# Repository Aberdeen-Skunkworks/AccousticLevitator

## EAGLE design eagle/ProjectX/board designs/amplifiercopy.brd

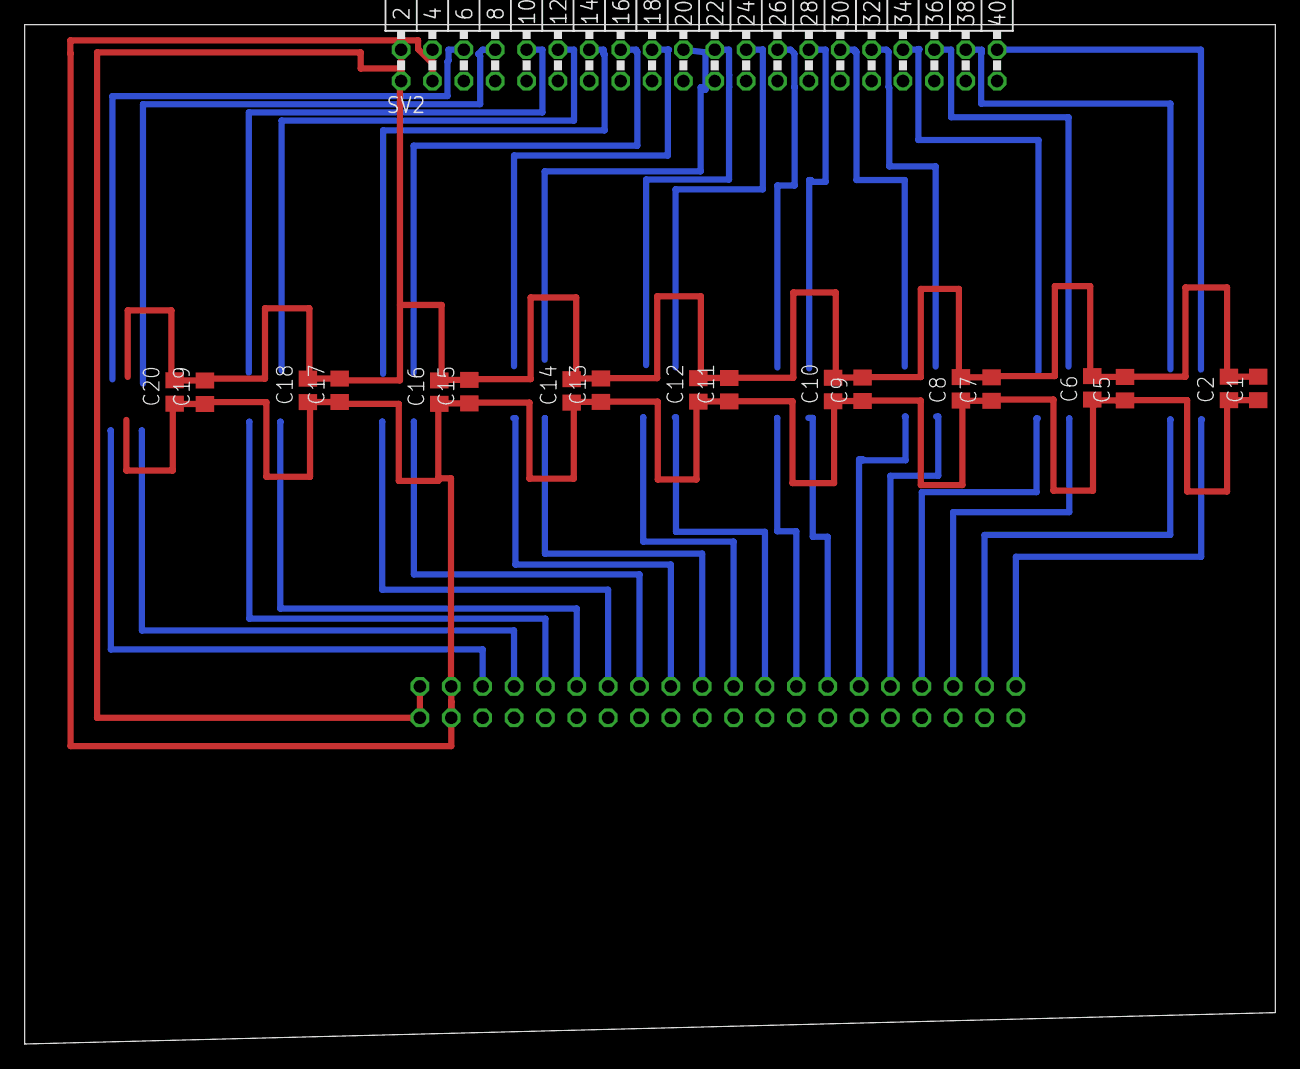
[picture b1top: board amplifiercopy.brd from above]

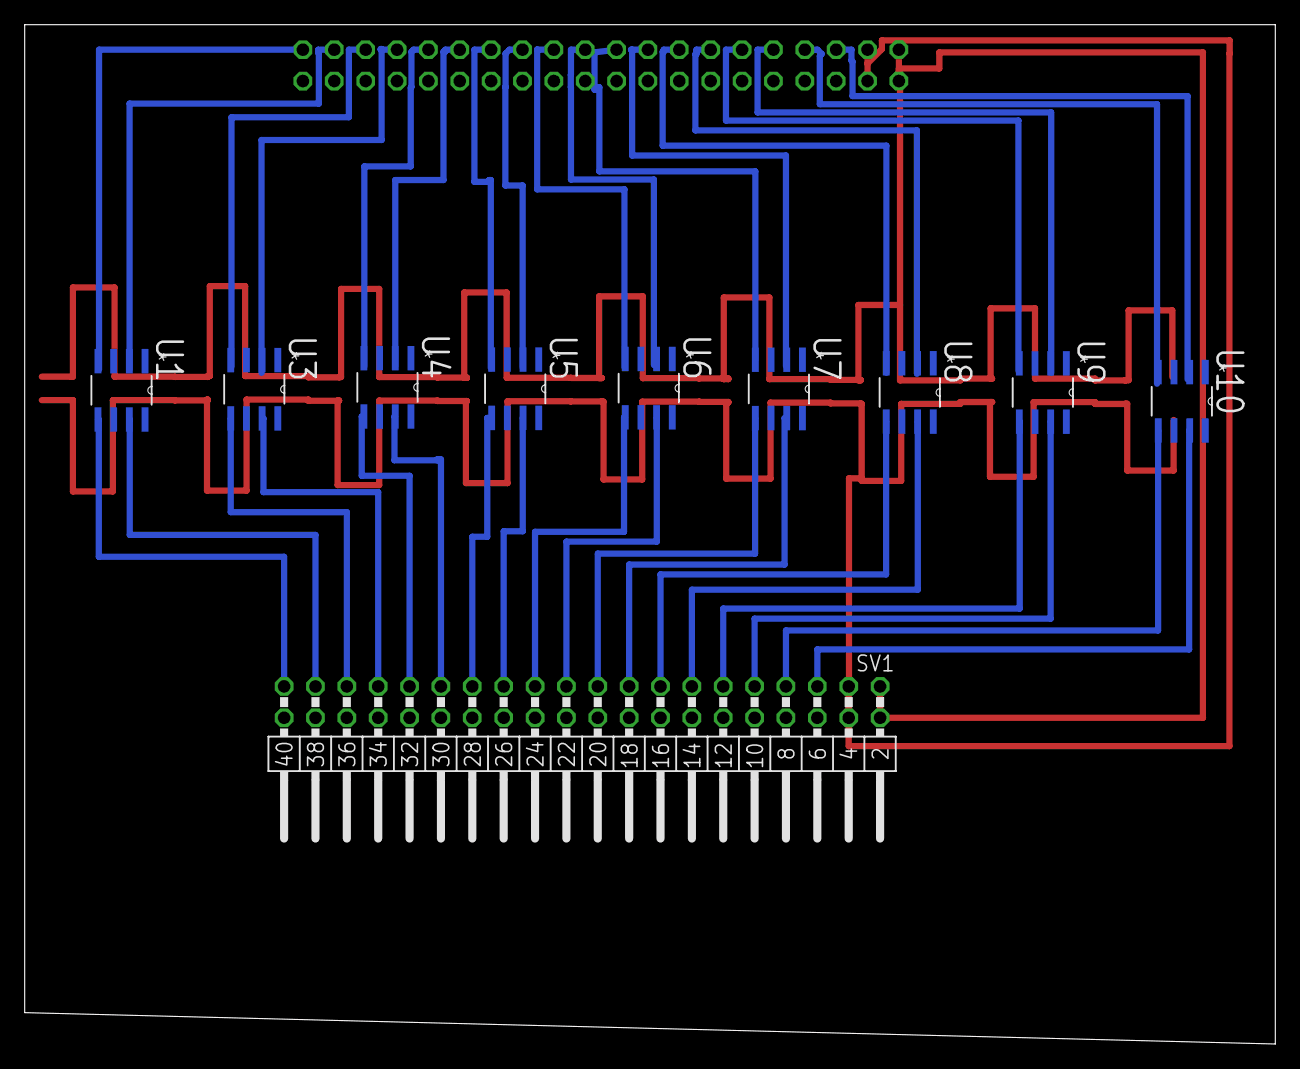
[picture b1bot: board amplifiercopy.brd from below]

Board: 2 copper layers, 101.3 x 82.5 mm, 29 parts (10 on the bottom side), 38 nets.

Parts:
C1, C5, C7, C9, C11, C13, C15, C17, C19: 4.7uF; C0805
C2, C6, C8, C10, C12, C14, C16, C18, C20: 100nF; C0805
SV1, SV2: MA20-2W
U1, U3, U4, U5, U6, U7, U8, U9, U10: TC4427COA; SOIC127P600X175-8N

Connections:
GND: C1.2, C2.2, C5.2, C6.2, C7.2, C8.2, C9.2, C10.2, C11.2, C12.2, C13.2, C14.2, C15.2, C16.2, C17.2, C18.2, C19.2, C20.2, SV1.1, SV1.2, SV2.1, SV2.2, U1.3, U3.3, U4.3, U5.3, U6.3, U7.3, U8.3, U9.3, U10.3
unnamed: SV2.36, U3.4
unnamed: SV1.39, U1.5
unnamed: SV1.37, U1.7
unnamed: SV2.40, U1.4
unnamed: SV2.38, U1.2
unnamed: SV2.34, U3.2
unnamed: SV1.35, U3.5
unnamed: SV1.33, U3.7
unnamed: SV2.32, U4.4
unnamed: SV2.30, U4.2
unnamed: SV1.31, U4.5
unnamed: SV1.29, U4.7
unnamed: SV1.27, U5.5
unnamed: SV1.25, U5.7
unnamed: SV2.28, U5.4
unnamed: SV2.26, U5.2
unnamed: SV1.23, U6.5
unnamed: SV1.21, U6.7
unnamed: SV2.24, U6.4
unnamed: SV2.22, U6.2
unnamed: SV1.19, U7.5
unnamed: SV1.17, U7.7
unnamed: SV2.20, U7.4
unnamed: SV1.15, U8.5
unnamed: SV1.13, U8.7
unnamed: SV2.18, U7.2
unnamed: SV2.16, U8.4
unnamed: SV2.14, U8.2
unnamed: SV2.12, U9.4
unnamed: SV1.11, U9.5
unnamed: SV1.9, U9.7
unnamed: SV2.10, U9.2
unnamed: SV2.8, U10.4
unnamed: SV1.5, U10.7
unnamed: SV1.7, U10.5
unnamed: SV2.6, U10.2
VCC: C1.1, C2.1, C5.1, C6.1, C7.1, C8.1, C9.1, C10.1, C11.1, C12.1, C13.1, C14.1, C15.1, C16.1, C17.1, C18.1, C19.1, C20.1, SV1.3, SV1.4, SV2.3, SV2.4, U1.6, U3.6, U4.6, U5.6, U6.6, U7.6, U8.6, U9.6, U10.6

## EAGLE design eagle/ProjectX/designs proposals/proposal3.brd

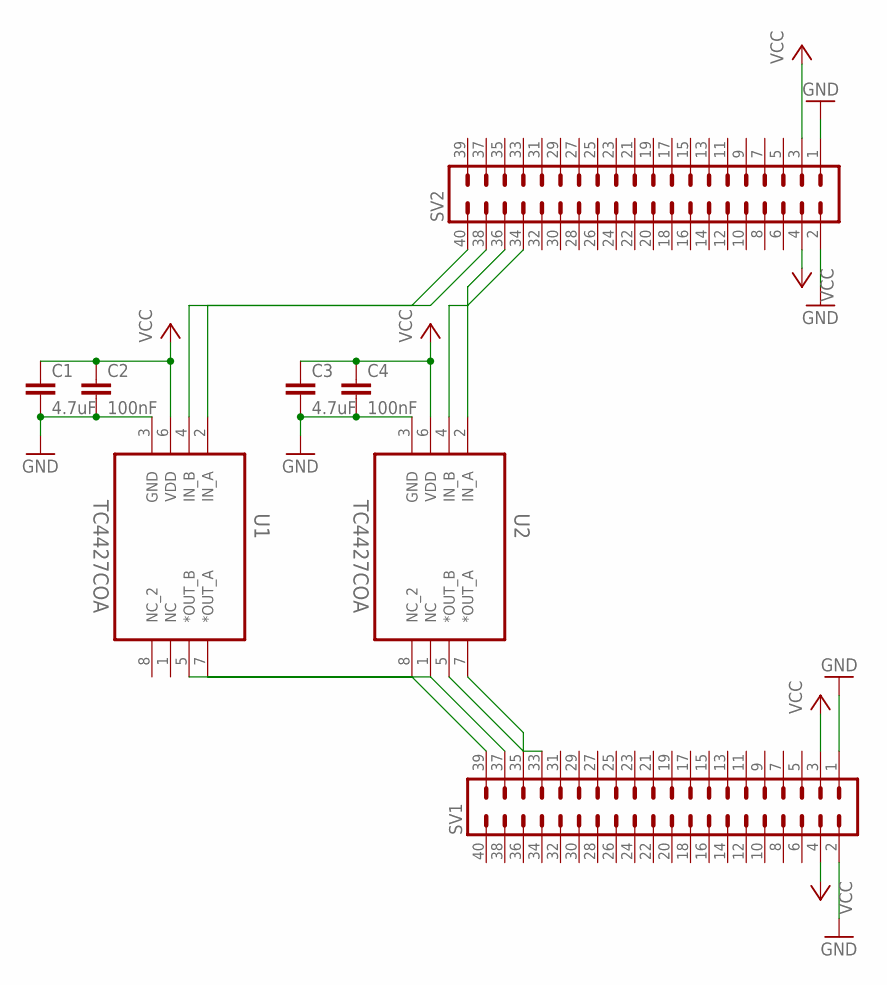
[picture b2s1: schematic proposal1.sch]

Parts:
C1, C3: 4.7uF; C0805
C2, C4: 100nF; C0805
SV1, SV2: MA20-2W
U1, U2: TC4427COA; SOIC127P600X175-8N

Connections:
GND: C1.2, C2.2, C3.2, C4.2, SV1.1, SV1.2, SV2.1, SV2.2, U1.3 (GND), U2.3 (GND)
unnamed: SV2.34, U2.4 (IN_B)
unnamed: SV1.39, U1.7 (*OUT_A)
unnamed: SV1.37, U1.5 (*OUT_B)
unnamed: SV2.38, U1.4 (IN_B)
unnamed: SV2.40, U1.2 (IN_A)
unnamed: SV2.36, U2.2 (IN_A)
unnamed: SV1.35, U2.7 (*OUT_A)
unnamed: SV1.33, U2.5 (*OUT_B)
VCC: C1.1, C2.1, C3.1, C4.1, SV1.3, SV1.4, SV2.3, SV2.4, U1.6 (VDD), U2.6 (VDD)

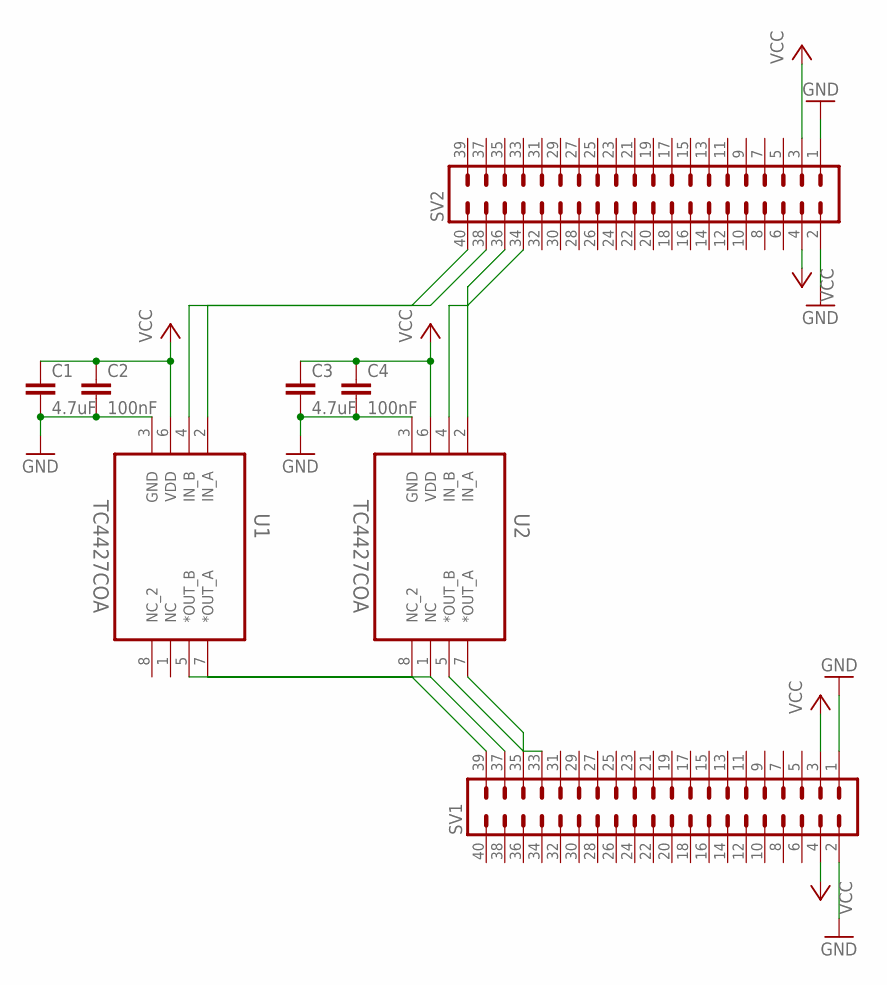
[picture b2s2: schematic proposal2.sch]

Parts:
C1, C3: 4.7uF; C0805
C2, C4: 100nF; C0805
SV1, SV2: MA20-2W
U1, U2: TC4427COA; SOIC127P600X175-8N

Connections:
GND: C1.2, C2.2, C3.2, C4.2, SV1.1, SV1.2, SV2.1, SV2.2, U1.3 (GND), U2.3 (GND)
unnamed: SV2.34, U2.4 (IN_B)
unnamed: SV1.39, U1.7 (*OUT_A)
unnamed: SV1.37, U1.5 (*OUT_B)
unnamed: SV2.38, U1.4 (IN_B)
unnamed: SV2.40, U1.2 (IN_A)
unnamed: SV2.36, U2.2 (IN_A)
unnamed: SV1.35, U2.7 (*OUT_A)
unnamed: SV1.33, U2.5 (*OUT_B)
VCC: C1.1, C2.1, C3.1, C4.1, SV1.3, SV1.4, SV2.3, SV2.4, U1.6 (VDD), U2.6 (VDD)

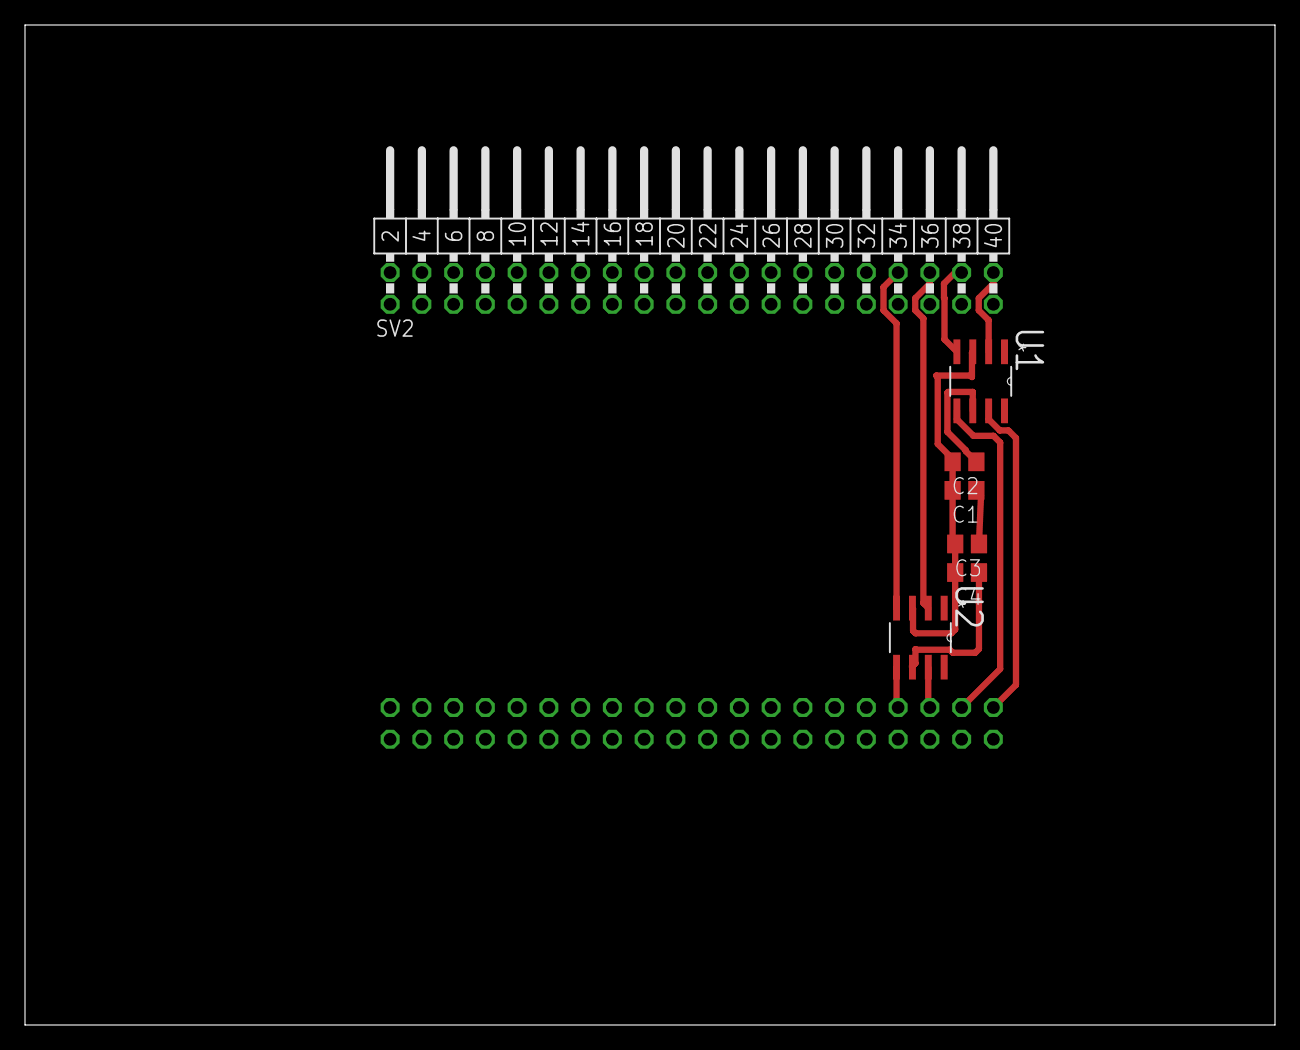
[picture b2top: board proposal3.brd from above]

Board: 2 copper layers, 100.0 x 80.0 mm, 8 parts (1 on the bottom side), 10 nets.

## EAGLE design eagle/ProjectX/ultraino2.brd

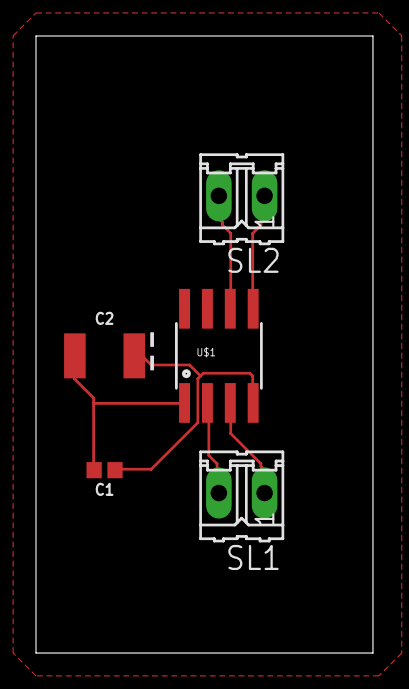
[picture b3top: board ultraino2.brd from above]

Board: 2 copper layers, 18.7 x 34.3 mm, 5 parts (0 on the bottom side), 6 nets.

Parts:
C1: 0.1uF; 0402
C2: 47uF; EIA3528
SL1, SL2: 02P
U$1: TC4427; SOIC-8

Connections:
unnamed: SL1.2, U$1.2
unnamed: SL1.1, U$1.3
unnamed: SL2.1, U$1.5
unnamed: SL2.2, U$1.6
PE: C1.1, C2.A, U$1.4
VCC: C1.2, C2.C, U$1.1

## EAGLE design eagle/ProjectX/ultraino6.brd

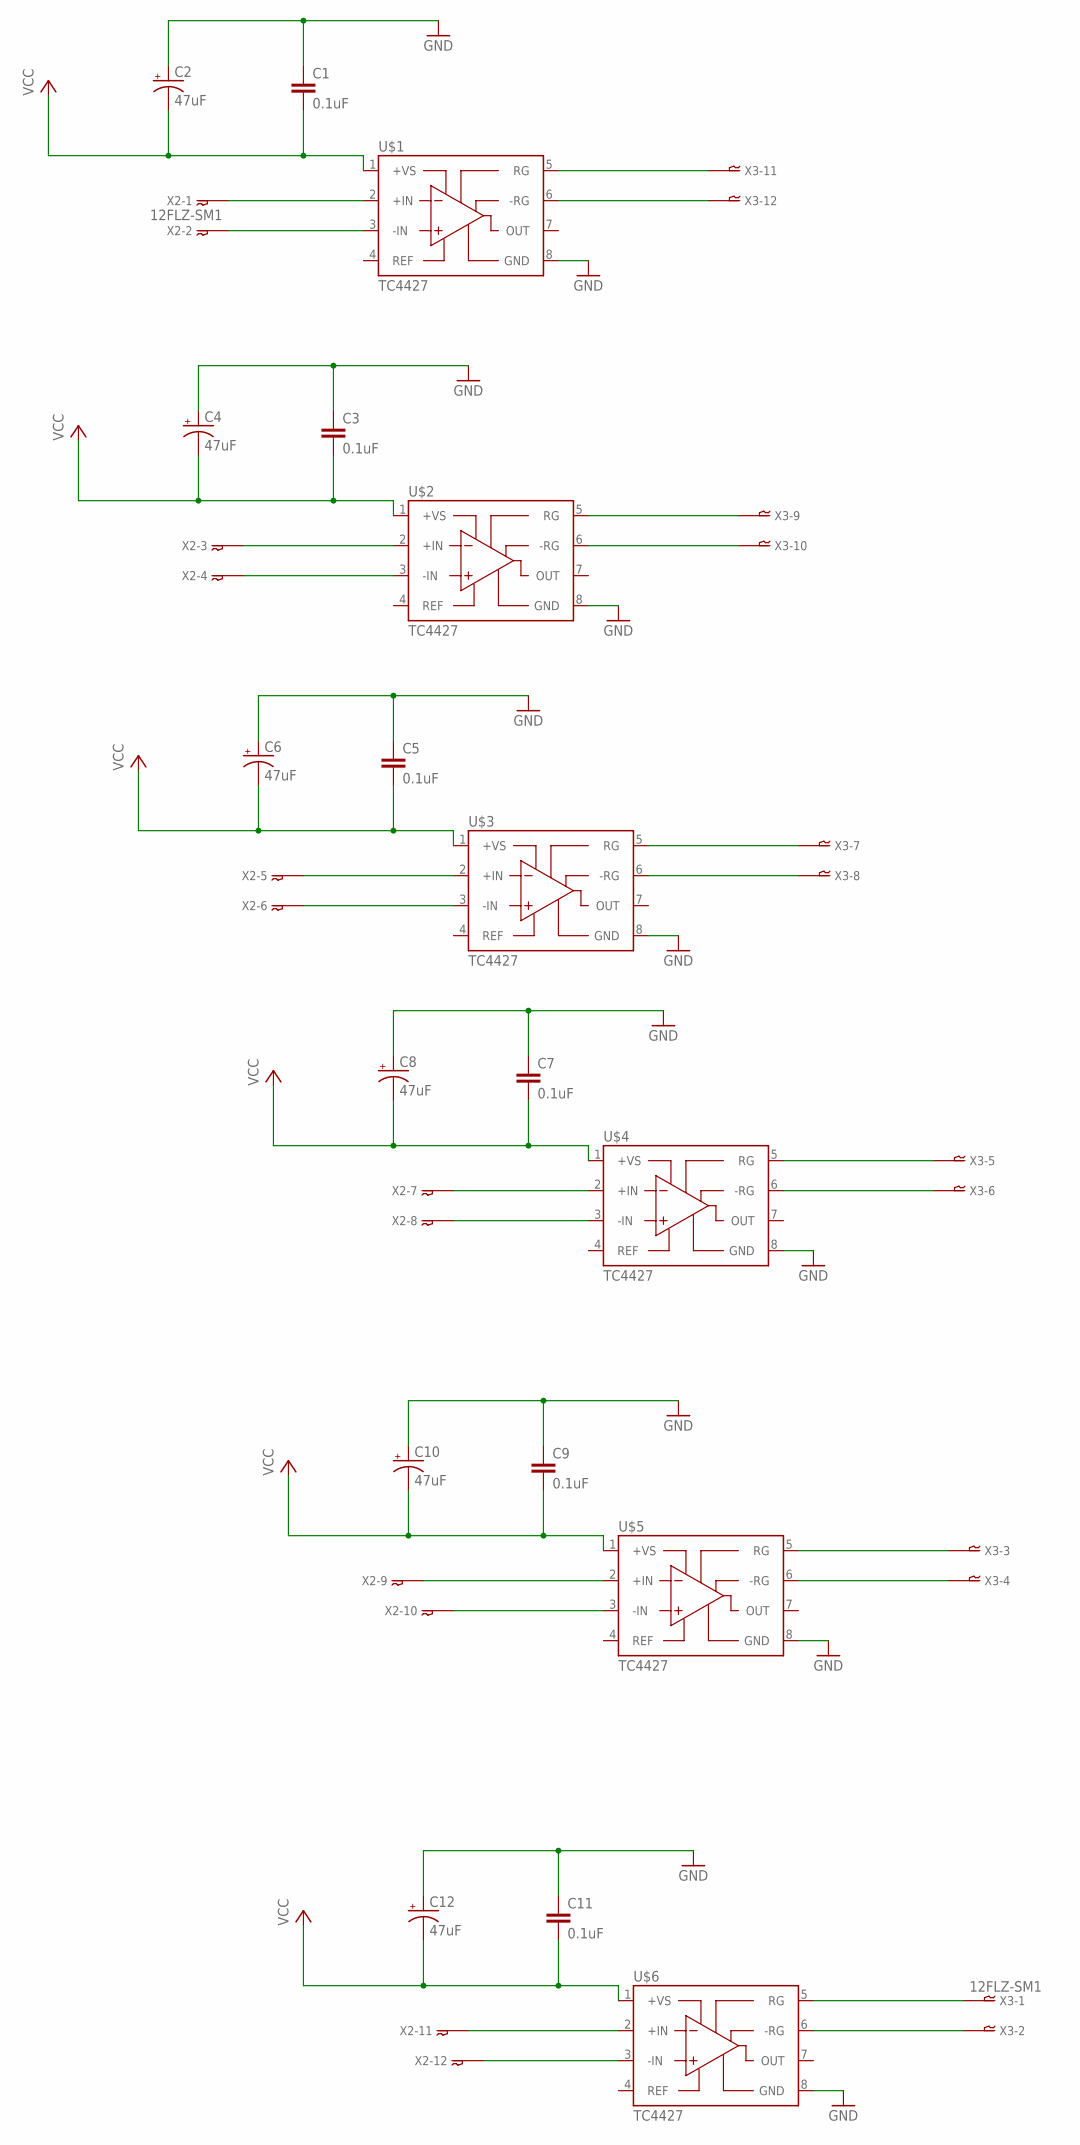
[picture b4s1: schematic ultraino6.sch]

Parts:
C1, C3, C5, C7, C9, C11: 0.1uF; 0402
C2, C4, C6, C8, C10, C12: 47uF; EIA3528
U$1, U$2, U$3, U$4, U$5, U$6: TC4427; SOIC-8
X2, X3: 12FLZ-SM1; 12FLZ-SM

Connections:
GND: C1.1, C2.A (+), C3.1, C4.A (+), C5.1, C6.A (+), C7.1, C8.A (+), C9.1, C10.A (+), C11.1, C12.A (+), U$1.8 (GND), U$2.8 (GND), U$3.8 (GND), U$4.8 (GND), U$5.8 (GND), U$6.8 (GND)
unnamed: U$1.2 (+IN), X2.1
unnamed: U$1.3 (-IN), X2.2
unnamed: U$1.5 (RG), X3.11
unnamed: U$1.6 (-RG), X3.12
unnamed: U$2.2 (+IN), X2.3
unnamed: U$2.5 (RG), X3.9
unnamed: U$2.6 (-RG), X3.10
unnamed: U$2.3 (-IN), X2.4
unnamed: U$3.2 (+IN), X2.5
unnamed: U$3.5 (RG), X3.7
unnamed: U$3.6 (-RG), X3.8
unnamed: U$3.3 (-IN), X2.6
unnamed: U$4.2 (+IN), X2.7
unnamed: U$4.5 (RG), X3.5
unnamed: U$4.6 (-RG), X3.6
unnamed: U$4.3 (-IN), X2.8
unnamed: U$5.2 (+IN), X2.9
unnamed: U$5.5 (RG), X3.3
unnamed: U$5.6 (-RG), X3.4
unnamed: U$5.3 (-IN), X2.10
unnamed: U$6.2 (+IN), X2.11
unnamed: U$6.5 (RG), X3.1
unnamed: U$6.6 (-RG), X3.2
unnamed: U$6.3 (-IN), X2.12
VCC: C1.2, C2.C (-), C3.2, C4.C (-), C5.2, C6.C (-), C7.2, C8.C (-), C9.2, C10.C (-), C11.2, C12.C (-), U$1.1 (+VS), U$2.1 (+VS), U$3.1 (+VS), U$4.1 (+VS), U$5.1 (+VS), U$6.1 (+VS)

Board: 2 copper layers, 20 parts (0 on the bottom side), 26 nets, no tracks yet.

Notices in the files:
parts and their libraries:
capacitor: Licensing: Creative Commons ShareAlike 4.0 International - https://creativecommons.org/licenses/by-sa/4.0
